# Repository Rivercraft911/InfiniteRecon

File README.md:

# InfiniteRecon
A lot coming soon....

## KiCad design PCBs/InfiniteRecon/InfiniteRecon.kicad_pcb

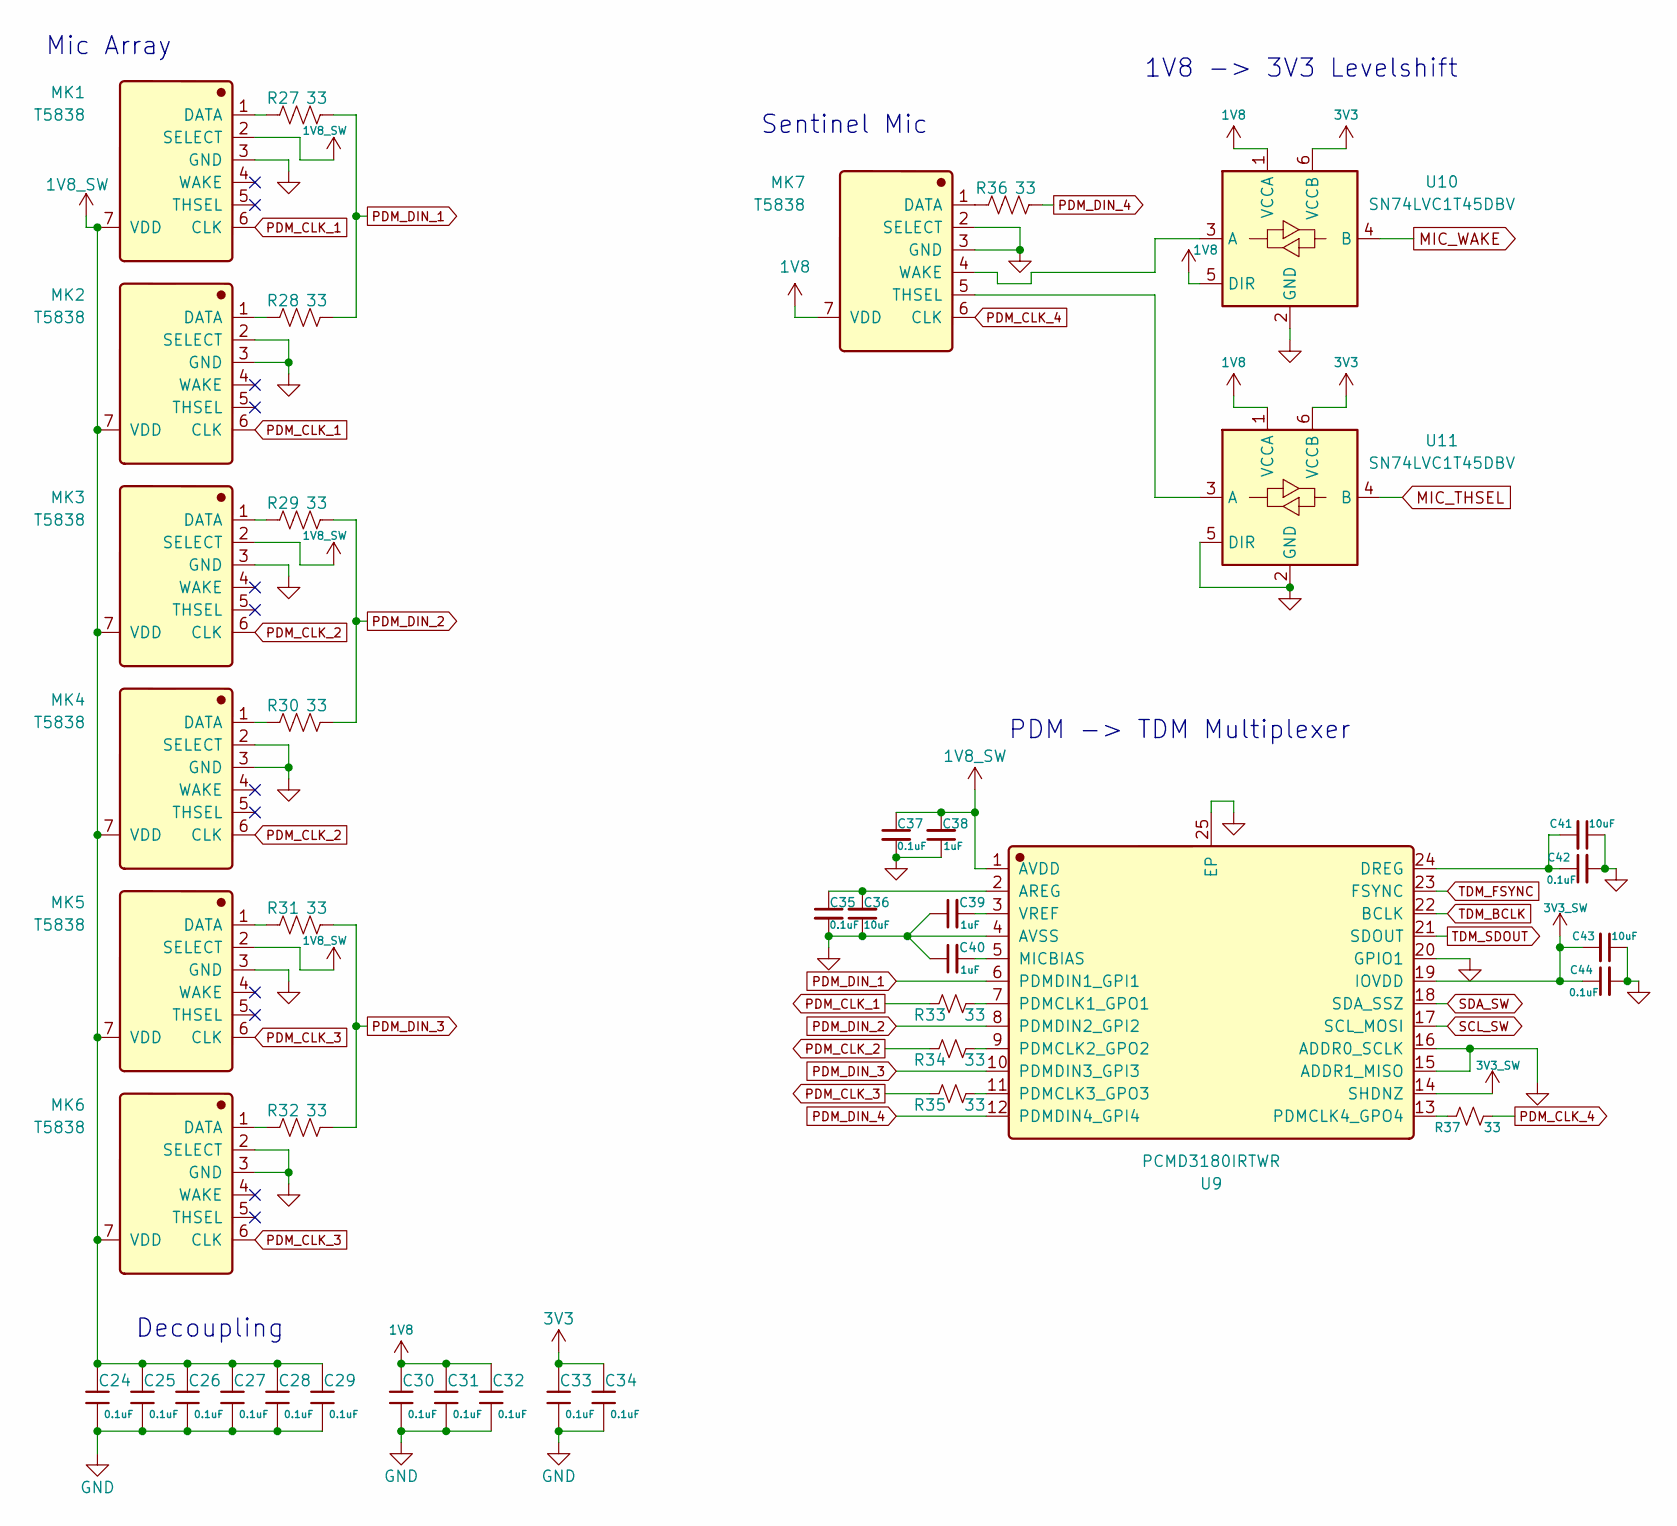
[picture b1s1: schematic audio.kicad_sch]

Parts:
C24, C25, C26, C27, C28, C29, C30, C31, C32, C33, C34, C35, C37, C42, C44: 0.1uF; C_0402; Voltage Rated 16V; Tolerance ±10%; Part CL05B104KO5NNNC; LCSC C1525
C36, C41, C43: 10uF; C_0603; Voltage Rated 10V; Tolerance ±10%; Part CL10A106KP8NNNC; LCSC C19702
C38, C39, C40: 1uF; C_0603; Voltage Rated 50V; Tolerance ±10%; Part CL10A105KB8NNNC; LCSC C15849
MK1, MK2, MK3, MK4, MK5, MK6, MK7: T5838; MIC_T5838; PARTREV 1.1; LCSC C7230692
R27, R28, R29, R30, R31, R32, R33, R34, R35, R36, R37: 33; R_0402_1005Metric
U9: PCMD3180IRTWR; WQFN-24-1EP_4x4mm_P0.5mm_EP2.45x2.45mm_ThermalVias; Manufacturer Part PCMD3180IRTWR; LCSC C2844195
U10, U11: SN74LVC1T45DBV; SOT-23-6; LCSC C7843

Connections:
1V8: C30.1, C31.1, C32.1, MK7.7 (VDD), U10.1 (VCCA), U10.5 (DIR), U11.1 (VCCA); also elsewhere on the board
1V8_SW: C24.1, C25.1, C26.1, C27.1, C28.1, C29.1, C37.1, C38.2, MK1.2 (SELECT), MK1.7 (VDD), MK2.7 (VDD), MK3.2 (SELECT), MK3.7 (VDD), MK4.7 (VDD), MK5.2 (SELECT), MK5.7 (VDD), MK6.7 (VDD), U9.1 (AVDD); also elsewhere on the board
3V3: C33.1, C34.1, U10.6 (VCCB), U11.6 (VCCB); also elsewhere on the board
3V3_SW: C43.2, C44.1, U9.14 (SHDNZ), U9.19 (IOVDD); also elsewhere on the board
GND: C24.2, C25.2, C26.2, C27.2, C28.2, C29.2, C30.2, C31.2, C32.2, C33.2, C34.2, C35.2, C36.1, C37.2, C38.1, C39.1, C40.1, C41.1, C42.2, C43.1, C44.2, MK1.3 (GND), MK2.2 (SELECT), MK2.3 (GND), MK3.3 (GND), MK4.2 (SELECT), MK4.3 (GND), MK5.3 (GND), MK6.2 (SELECT), MK6.3 (GND), MK7.2 (SELECT), MK7.3 (GND), U9.4 (AVSS), U9.15 (ADDR1_MISO), U9.16 (ADDR0_SCLK), U9.20 (GPIO1), U9.25 (EP), U10.2 (GND), U11.2 (GND), U11.5 (DIR); also elsewhere on the board
MIC_THSEL: U11.4 (B); also elsewhere on the board
MIC_WAKE: U10.4 (B); also elsewhere on the board
unnamed: MK1.1 (DATA), R27.1
unnamed: MK2.1 (DATA), R28.1
unnamed: MK3.1 (DATA), R29.1
unnamed: MK4.1 (DATA), R30.1
unnamed: MK5.1 (DATA), R31.1
unnamed: MK6.1 (DATA), R32.1
unnamed: MK7.1 (DATA), R36.1
unnamed: MK7.5 (THSEL), U11.3 (A)
unnamed: MK7.4 (WAKE), U10.3 (A)
unnamed: C35.1, C36.2, U9.2 (AREG)
unnamed: C41.2, C42.1, U9.24 (DREG)
unnamed: C40.2, U9.5 (MICBIAS)
unnamed: R33.2, U9.7 (PDMCLK1_GPO1)
unnamed: R34.2, U9.9 (PDMCLK2_GPO2)
unnamed: R35.2, U9.11 (PDMCLK3_GPO3)
unnamed: R37.1, U9.13 (PDMCLK4_GPO4)
unnamed: C39.2, U9.3 (VREF)
PDM_CLK_1: MK1.6 (CLK), MK2.6 (CLK), R33.1
PDM_CLK_2: MK3.6 (CLK), MK4.6 (CLK), R34.1
PDM_CLK_3: MK5.6 (CLK), MK6.6 (CLK), R35.1
PDM_CLK_4: MK7.6 (CLK), R37.2
PDM_DIN_1: R27.2, R28.2, U9.6 (PDMDIN1_GPI1)
PDM_DIN_2: R29.2, R30.2, U9.8 (PDMDIN2_GPI2)
PDM_DIN_3: R31.2, R32.2, U9.10 (PDMDIN3_GPI3)
PDM_DIN_4: R36.2, U9.12 (PDMDIN4_GPI4)
SCL_SW: U9.17 (SCL_MOSI); also elsewhere on the board
SDA_SW: U9.18 (SDA_SSZ); also elsewhere on the board
TDM_BCLK: U9.22 (BCLK); also elsewhere on the board
TDM_FSYNC: U9.23 (FSYNC); also elsewhere on the board
TDM_SDOUT: U9.21 (SDOUT); also elsewhere on the board

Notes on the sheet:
Decoupling
PDM -> TDM Multiplexer
Sentinel Mic
1V8 -> 3V3 Levelshift
Mic Array

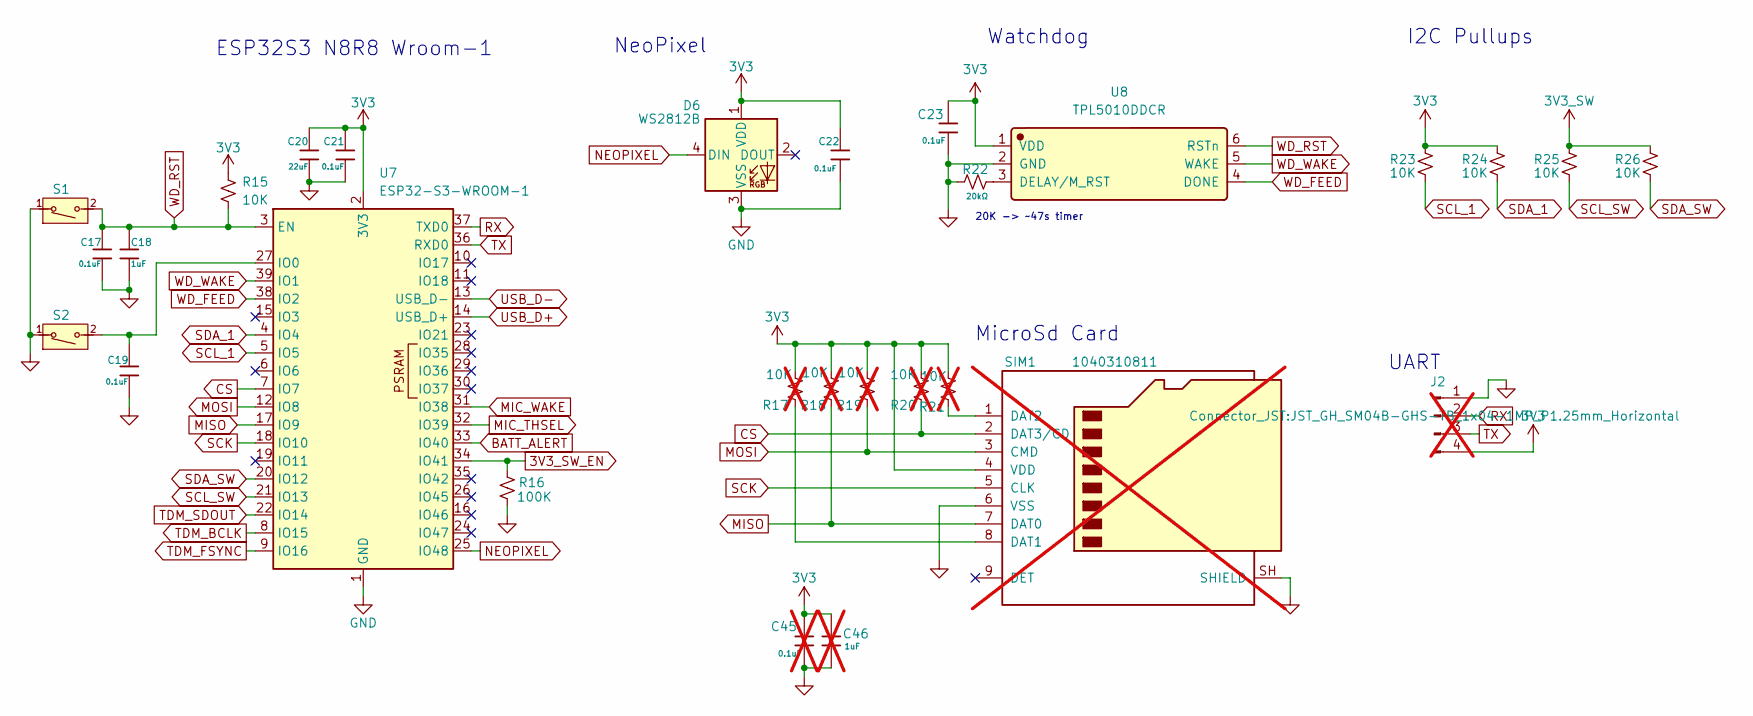
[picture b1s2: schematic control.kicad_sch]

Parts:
C17, C19, C21, C22, C23: 0.1uF; C_0402; Voltage Rated 16V; Tolerance ±10%; Part CL05B104KO5NNNC; LCSC C1525
C18: 1uF; C_0603; Voltage Rated 50V; Tolerance ±10%; Part CL10A105KB8NNNC; LCSC C15849
C20: 22uF; C_0805; Voltage Rated 25V; Tolerance ±20%; Part CL21A226MAQNNNE; LCSC C45783
C45: 0.1uF; C_0402; Voltage Rated 16V; Tolerance ±10%; Part CL05B104KO5NNNC; LCSC C1525; not fitted
C46: 1uF; C_0603; Voltage Rated 50V; Tolerance ±10%; Part CL10A105KB8NNNC; LCSC C15849; not fitted
D6: WS2812B; LED_WS2812B_PLCC4_5.0x5.0mm_P3.2mm
J2: Conn_01x04_Pin; JST_GH_SM04B-GHS-TB_1x04-1MP_P1.25mm_Horizontal; not fitted
R15, R23, R24, R25, R26: 10K; R_0402_1005Metric
R16: 100K; R_0402_1005Metric
R17, R18, R19, R20, R21: 10K; R_0603_1608Metric_Pad0.98x0.95mm_HandSolder; not fitted
R22: 20kΩ; R_0402_1005Metric; Overload Voltage (Max) 50V; Tolerance ±1%; Part 0402WGF2002TCE; LCSC C25765
S1, S2: Tactile Button, 160gf; SW_TS-1088-AR02016; Voltage Rating (Dc) 12V; Part TS-1088-AR02016; LCSC C720477
SIM1: 1040310811; microSD_HC_Molex_104031-0811; Manufacturer Part 1040310811; LCSC C585350; not fitted
U7: ESP32-S3-WROOM-1; LCSC Part # C2913201
U8: TPL5010DDCR; SOT-23-6; Manufacturer Part TPL5010DDCR; LCSC C473912

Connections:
3V3: C20.1, C21.1, C22.1, C23.1, C45.1, C46.1, D6.1 (VDD), J2.4, R15.1, R17.1, R18.1, R19.1, R20.1, R21.1, R23.1, R24.1, SIM1.4 (VDD), U7.2 (3V3), U8.1 (VDD); also elsewhere on the board
3V3_SW: R25.1, R26.1; also elsewhere on the board
3V3_SW_EN: R16.1, U7.34 (IO41); also elsewhere on the board
BATT_ALERT: U7.33 (IO40); also elsewhere on the board
CS: R20.2, SIM1.2 (DAT3/CD), U7.7 (IO7)
GND: C17.2, C18.2, C19.2, C20.2, C21.2, C22.2, C23.2, C45.2, C46.2, D6.3 (VSS), J2.1, R16.2, R22.1, S1.1 (A), S2.1 (A), SIM1.6 (VSS), SIM1.SH (SHIELD), U7.1 (GND), U7.40 (GND), U7.41 (GND), U8.2 (GND); also elsewhere on the board
MIC_THSEL: U7.32 (IO39); also elsewhere on the board
MIC_WAKE: U7.31 (IO38); also elsewhere on the board
MISO: R18.2, SIM1.7 (DAT0), U7.17 (IO9)
MOSI: R19.2, SIM1.3 (CMD), U7.12 (IO8)
NEOPIXEL: D6.4 (DIN), U7.25 (IO48)
unnamed: C19.1, S2.2 (B), U7.27 (IO0)
unnamed: R17.2, SIM1.8 (DAT1)
unnamed: R21.2, SIM1.1 (DAT2)
unnamed: R22.2, U8.3 (DELAY/M_RST)
RX: J2.2, U7.37 (TXD0)
SCK: SIM1.5 (CLK), U7.18 (IO10)
SCL_1: R23.2, U7.5 (IO5); also elsewhere on the board
SCL_SW: R25.2, U7.21 (IO13); also elsewhere on the board
SDA_1: R24.2, U7.4 (IO4); also elsewhere on the board
SDA_SW: R26.2, U7.20 (IO12); also elsewhere on the board
TDM_BCLK: U7.8 (IO15); also elsewhere on the board
TDM_FSYNC: U7.9 (IO16); also elsewhere on the board
TDM_SDOUT: U7.22 (IO14); also elsewhere on the board
TX: J2.3, U7.36 (RXD0)
USB_D+: U7.14 (USB_D+); also elsewhere on the board
USB_D-: U7.13 (USB_D-); also elsewhere on the board
WD_FEED: U7.38 (IO2), U8.4 (DONE)
WD_RST: C17.1, C18.1, R15.2, S1.2 (B), U7.3 (EN), U8.6 (RSTn)
WD_WAKE: U7.39 (IO1), U8.5 (WAKE)

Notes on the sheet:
ESP32S3 N8R8 Wroom-1
20K -> ~47s timer
MicroSd Card
NeoPixel
I2C Pullups
UART
Watchdog

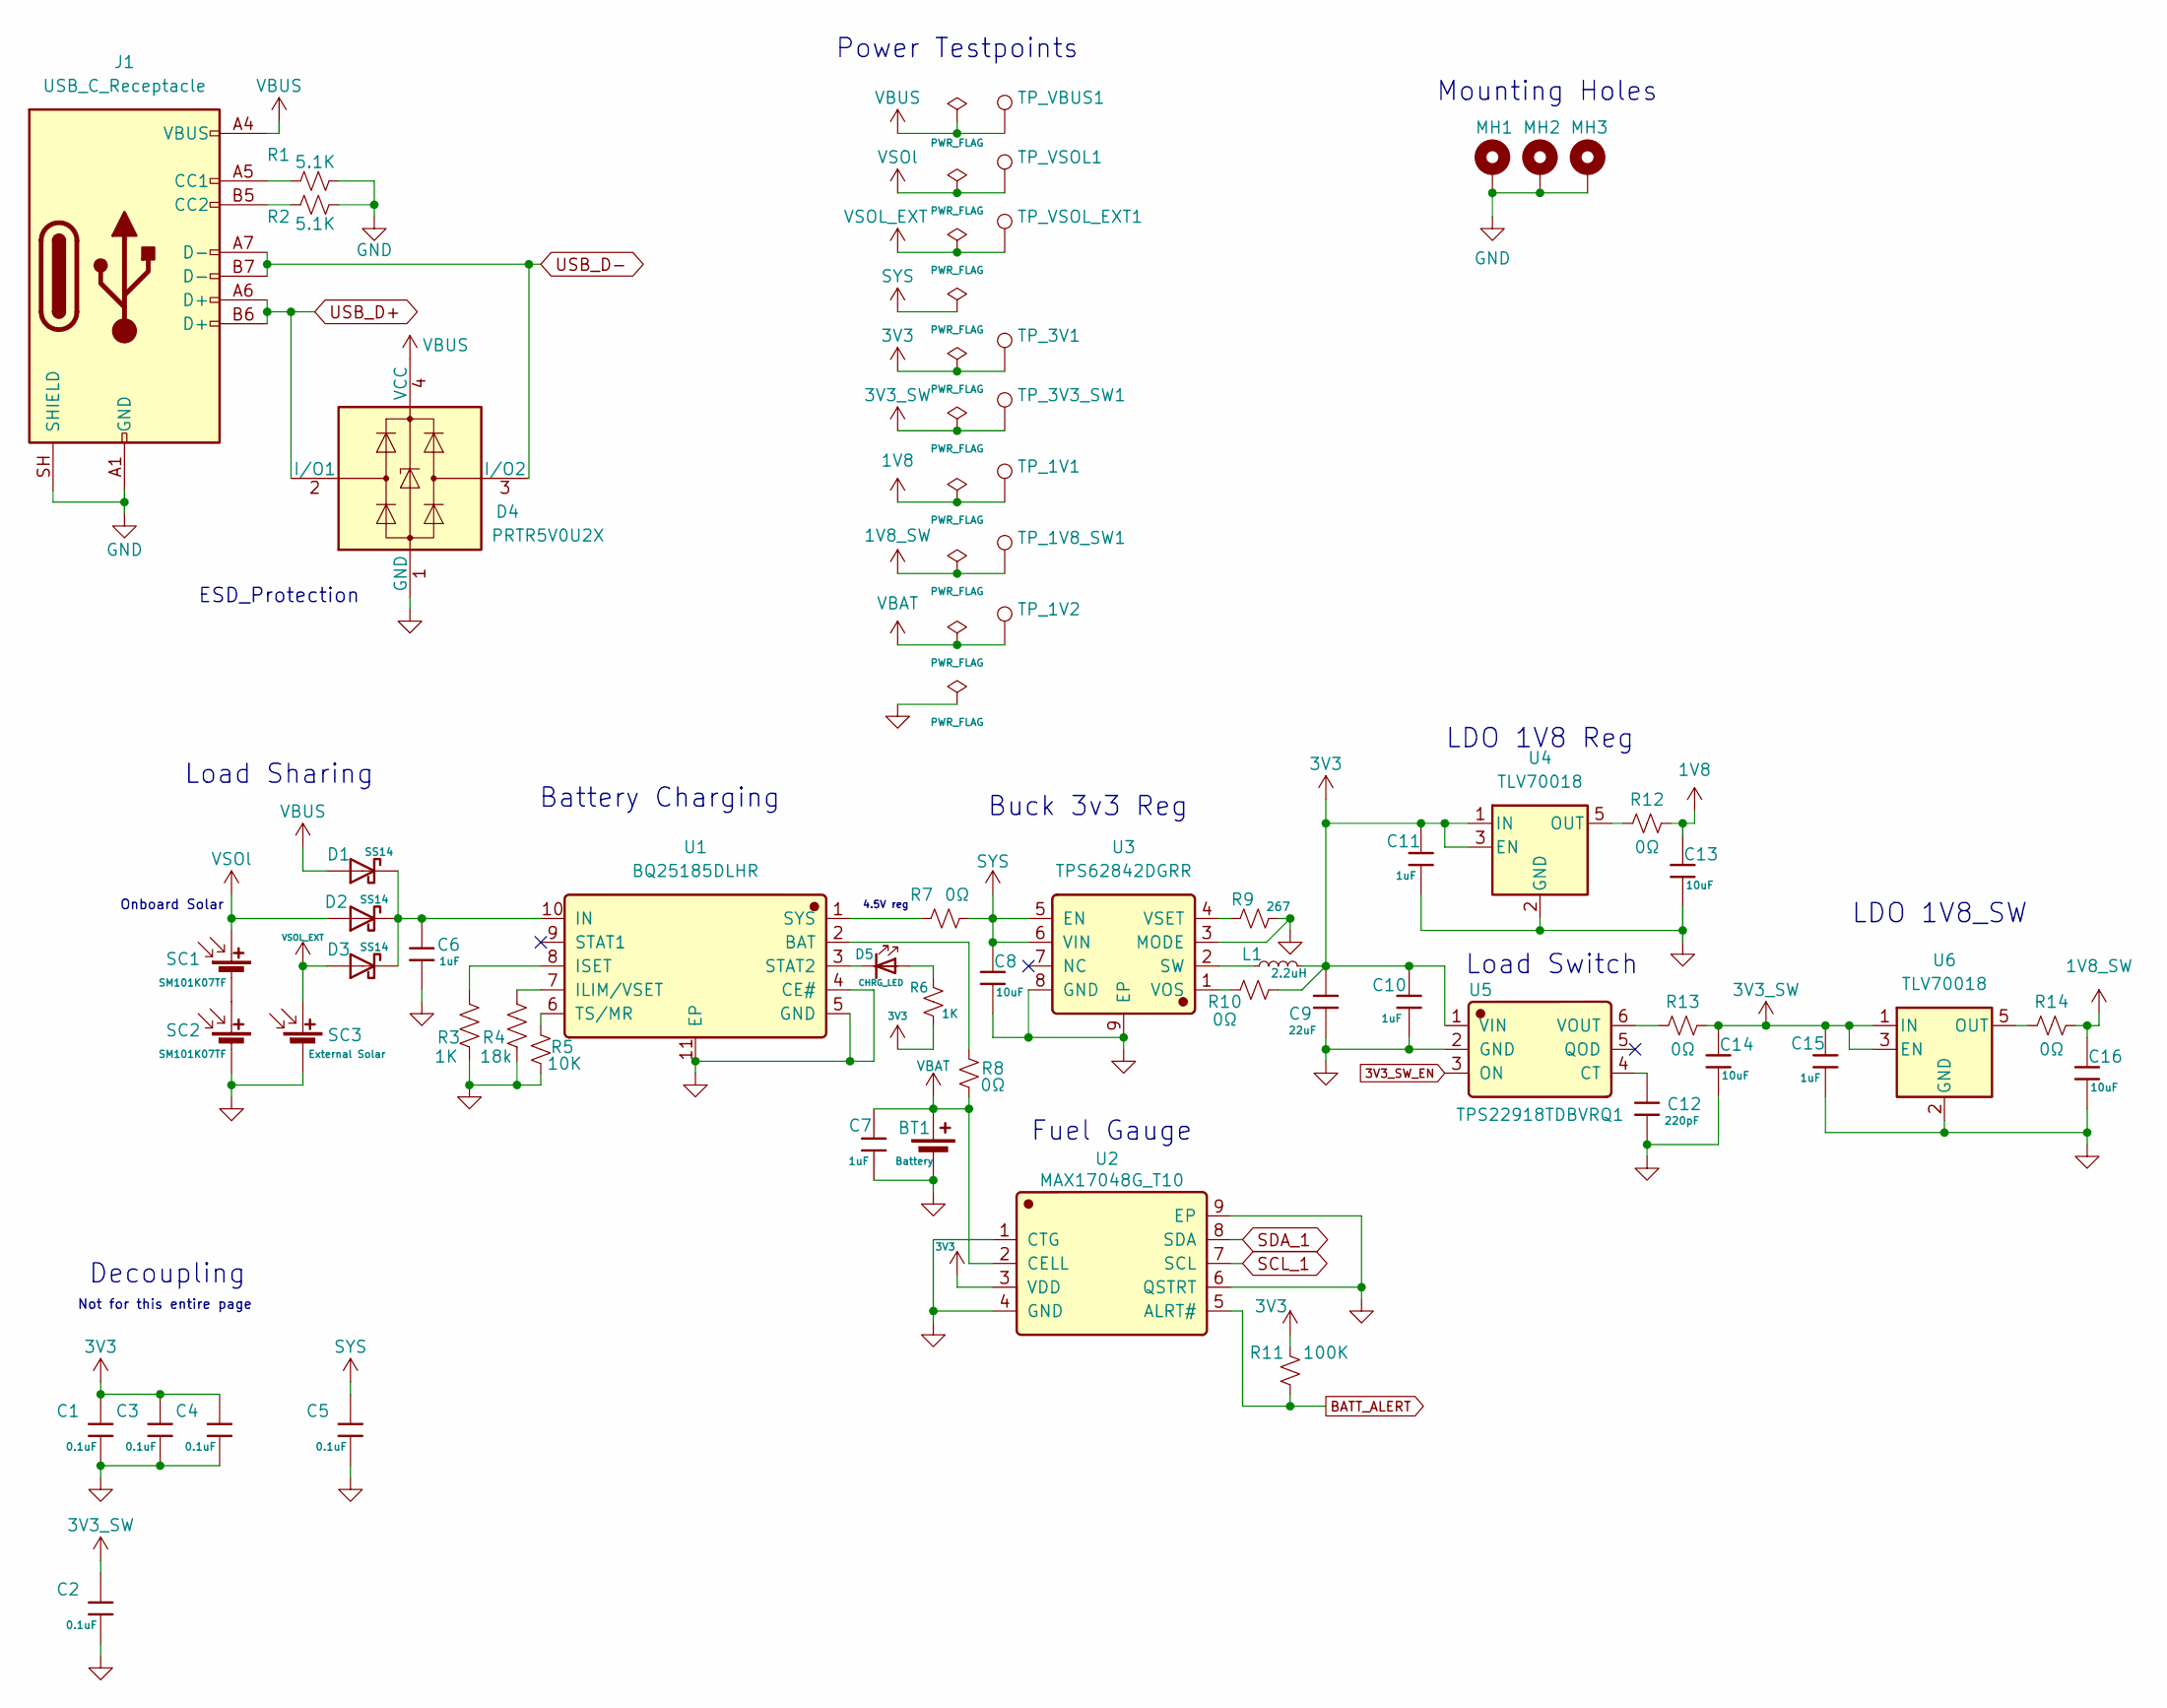
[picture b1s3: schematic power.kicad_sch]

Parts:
BT1: Battery; JST_PH_S2B-PH-SM4-TB_1x02-1MP_P2.00mm_Horizontal
C1, C2, C3, C4, C5: 0.1uF; C_0402; Voltage Rated 16V; Tolerance ±10%; Part CL05B104KO5NNNC; LCSC C1525
C6, C7, C10, C11, C15: 1uF; C_0603; Voltage Rated 50V; Tolerance ±10%; Part CL10A105KB8NNNC; LCSC C15849
C8, C13, C14, C16: 10uF; C_0603; Voltage Rated 10V; Tolerance ±10%; Part CL10A106KP8NNNC; LCSC C19702
C9: 22uF; C_0805; Voltage Rated 25V; Tolerance ±20%; Part CL21A226MAQNNNE; LCSC C45783
C12: 220pF; C_0402; Voltage Rated 50V; Tolerance ±10%; Part 0402B221K500NT; LCSC C1530
D1, D2, D3: SS14; D_SMA; Forward Voltage (Vf@If) 550mV@1A; Reverse Voltage (Vr) 40V; Part SS14; LCSC C2480
D4: PRTR5V0U2X; SOT-143
D5: CHRG_LED; D_0805; Part KT-0805G; LCSC C2297
J1: USB_C_Receptacle; USB_C_Receptacle_GCT_USB4105-xx-A_16P_TopMnt_Horizontal
L1: 2.2uH; OSC-SMD_L5.0-W3.2; Manufacturer Part FNR3015S2R2MT; LCSC C167747
MH1, MH2, MH3: MountingHole_Pad; MountingHole_2.2mm_M2_DIN965_Pad
R1, R2: 5.1K; R_0402_1005Metric
R3: 1K; R_0402_1005Metric; LCSC C11702
R4: 18k; R_0402_1005Metric
R5: 10K; R_0402_1005Metric
R6: 1K; R_0402_1005Metric
R7, R8, R10, R12, R13, R14: 0Ω; R_0603_1608Metric_Pad0.98x0.95mm_HandSolder
R9: 267; R_0603_1608Metric
R11: 100K; R_0402_1005Metric
SC1, SC2: SM101K07TF
SC3: External Solar; JST_PH_S2B-PH-SM4-TB_1x02-1MP_P2.00mm_Horizontal
TP_1V1, TP_1V2, TP_1V8_SW1, TP_3V1, TP_3V3_SW1: TestPoint; TestPoint_Pad_1.5x1.5mm
TP_VBUS1: TestPoint; TestPoint_Pad_1.5x1.5mm
TP_VSOL1: TestPoint; TestPoint_Pad_1.5x1.5mm
TP_VSOL_EXT1: TestPoint; TestPoint_Pad_1.5x1.5mm
U1: BQ25185DLHR; Texas_DLH0010A_WSON-10-1EP_2.2x2mm_P0.4mm_EP0.9x1.5mm; Manufacturer Part BQ25185DLHR; LCSC C19725033
U2: MAX17048G_T10; DFN-8-1EP_2x2mm_P0.5mm_EP0.9x1.3mm; Manufacturer Part MAX17048G+T10; LCSC C2682616
U3: TPS62842DGRR; HVSSOP-8-1EP_3x3mm_P0.65mm_EP1.57x1.89mm_ThermalVias; Manufacturer Part TPS62842DGRR; LCSC C2873354
U4, U6: TLV70018; SOT-23-5
U5: TPS22918TDBVRQ1; SOT-23-6; Manufacturer Part TPS22918TDBVRQ1; LCSC C2653760

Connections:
1V8: C13.1, R12.1, TP_1V1.1 (1_1); also elsewhere on the board
1V8_SW: C16.1, R14.1, TP_1V8_SW1.1 (1_1); also elsewhere on the board
3V3: C1.1, C3.1, C4.1, C9.1, C10.1, C11.1, L1.2, R6.1, R10.2, R11.1, TP_3V1.1 (1_1), U2.3 (VDD), U4.1 (IN), U4.3 (EN), U5.1 (VIN); also elsewhere on the board
3V3_SW: C2.1, C14.1, C15.1, R13.1, TP_3V3_SW1.1 (1_1), U6.1 (IN), U6.3 (EN); also elsewhere on the board
3V3_SW_EN: U5.3 (ON); also elsewhere on the board
BATT_ALERT: R11.2, U2.5 (ALRT#); also elsewhere on the board
GND: BT1.2 (-), C1.2, C2.2, C3.2, C4.2, C5.2, C6.2, C7.2, C8.2, C9.2, C10.2, C11.2, C12.2, C13.2, C14.2, C15.2, C16.2, D4.1 (GND), J1.A1 (GND), J1.A12 (GND), J1.B1 (GND), J1.B12 (GND), J1.SH (SHIELD), MH1.1 (1_1), MH2.1 (1_1), MH3.1 (1_1), R1.2, R2.2, R3.2, R4.2, R5.2, R9.2, SC2.2 (-), SC3.2 (-), U1.4 (CE#), U1.5 (GND), U1.11 (EP), U2.1 (CTG), U2.4 (GND), U2.6 (QSTRT), U2.9 (EP), U3.3 (MODE), U3.8 (GND), U3.9 (EP), U4.2 (GND), U5.2 (GND), U6.2 (GND); also elsewhere on the board
unnamed: D5.2, R6.2
unnamed: J1.A5 (CC1), R1.1
unnamed: J1.B5 (CC2), R2.1
unnamed: SC1.2 (-), SC2.1 (+)
unnamed: R8.2, U1.2 (BAT)
unnamed: R4.1, U1.7 (ILIM/VSET)
unnamed: C6.1, D1.1, D2.1, D3.1, U1.10 (IN)
unnamed: R3.1, U1.8 (ISET)
unnamed: D5.1, U1.3 (STAT2)
unnamed: R7.1, U1.1 (SYS)
unnamed: R5.1, U1.6 (TS/MR)
unnamed: L1.1, U3.2 (SW)
unnamed: R10.1, U3.1 (VOS)
unnamed: R9.1, U3.4 (VSET)
unnamed: R12.2, U4.5 (OUT)
unnamed: C12.1, U5.4 (CT)
unnamed: R13.2, U5.6 (VOUT)
unnamed: R14.2, U6.5 (OUT)
SCL_1: U2.7 (SCL); also elsewhere on the board
SDA_1: U2.8 (SDA); also elsewhere on the board
SYS: C5.1, C8.1, R7.2, U3.5 (EN), U3.6 (VIN)
USB_D+: D4.2 (I/O1), J1.A6 (D+), J1.B6 (D+); also elsewhere on the board
USB_D-: D4.3 (I/O2), J1.A7 (D-), J1.B7 (D-); also elsewhere on the board
VBAT: BT1.1 (+), C7.1, R8.1, TP_1V2.1 (1_1), U2.2 (CELL)
VBUS: D1.2, D4.4 (VCC), J1.A4 (VBUS), J1.A9 (VBUS), J1.B4 (VBUS), J1.B9 (VBUS), TP_VBUS1.1 (1_1)
VSOL_EXT: D3.2, SC3.1 (+), TP_VSOL_EXT1.1 (1_1)
VSOl: D2.2, SC1.1 (+), TP_VSOL1.1 (1_1)

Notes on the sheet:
Battery Charging
Power Testpoints
Fuel Gauge
LDO 1V8 Reg
ESD_Protection
4.5V reg
Mounting Holes
Decoupling
Buck 3v3 Reg
Onboard Solar
Not for this entire page
Load Sharing
LDO 1V8_SW
Load Switch

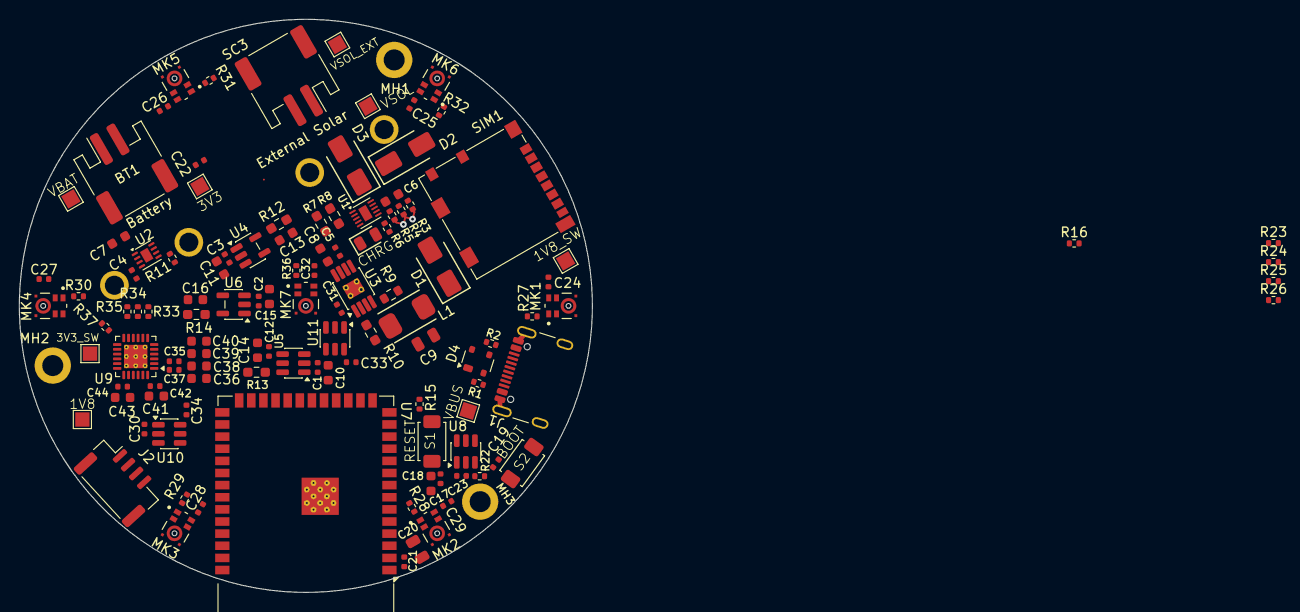
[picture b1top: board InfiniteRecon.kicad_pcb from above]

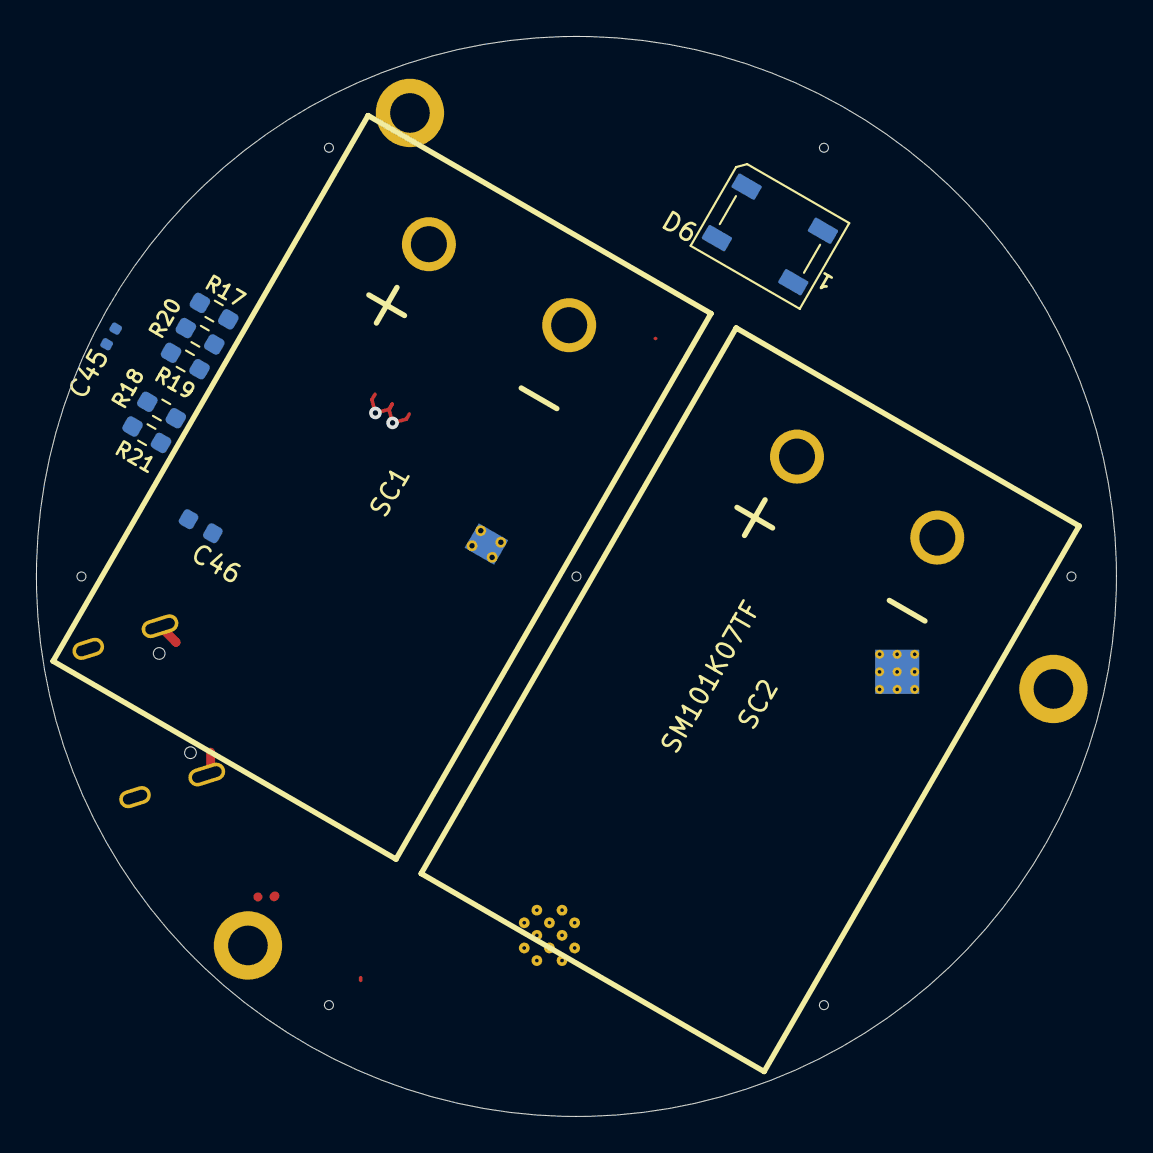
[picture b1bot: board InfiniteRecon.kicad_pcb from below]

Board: 4 copper layers, 60.0 x 60.0 mm, 128 parts (10 on the bottom side), 80 nets.

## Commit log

2025-02-05 Updated Firmware & Server
2025-02-05 Sep Python Files, addedLLM section, HTML updated, readme updated, req.txt created
2025-02-05 Added web_server.py
2026-02-12 Update README.md
    Removed Raspberry Pi setup instructions and security notes from README.
2026-03-26 AddedInitBoardFiles
2026-03-26 Added some starter stuffs
2026-03-26 Added USBC, Batt Charg, Load Switching Circuits
2026-03-28 Finished Scem for the most part, awake me needs to look it over one more time
2026-03-29 Fixed footprints and some not connected caps
2026-03-29 Finished scem
2026-03-29 Reanotated
2026-03-29 Added Mics
2026-03-29 lots of routing to be done
    maybe its time to descope...
2026-03-30 More layout
2026-04-02 Layout more or less done. Still missing i2c pullups and need to redo pinout
